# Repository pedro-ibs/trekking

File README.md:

# Trekking project
Desenvolvimento de um robô rádio-controlado/autônomo da moralidade “trekking”

Nos arquivos [anteriores-descontinuados](./anteriores-descontinuados/) e nos demais arquivos deste repositório podem conter os termos `rv1` e `rv2` eles estão referindo a versões anteriores do robô sendo `Robô versão 1` `Robô versão 2`.

<br>

Apresentações anteriores relaionadas:
 * [**#CPBR16** - Trabalhando com Unidades de medidas Inerciais (IMU) ](https://garoa.net.br/wiki/Dumont_Hackerspace_na_Campus_Party_2024)
 * [ **#CPBR15** - Construindo um Robô Trekking - versão 2.0](https://www.youtube.com/watch?v=lGhopql1V54)
 * [ **#CPBR14** - Construção de um robo rádio controlado](https://www.youtube.com/watch?v=8P9nPsCdVAc)

<br> <br> <br>

### **Robô versão 3**:

<br>

### **Robô versão 2**: 

<br>

### **Robô versão 1**:

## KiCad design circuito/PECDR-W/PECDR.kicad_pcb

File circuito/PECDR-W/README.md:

# **PECDR** - **P**lataforma **E**letrónica de **C**ontrole **D**istribuído em **R**ede 

A proposta deste circuito é distribuir o controle em subsistemas utilizando rede sem fio ou por meio da comunicação RS485. Conta com a `raspberry pi pico` modelo comum ou `W`. e diversos periféricos possibilitando atuar em trabalhos variados.

### **Elementos**:
 * O circuito embarca uma `raspberry pi pico` modelo comum ou `W`;
 * Uma fonte dc-dc buck step down 3V3 3A;
 * Driver de potência  L298N (com seleção de tensão de operação entre VCC e 3V3);
 * Interface de comunicação RS485;
 * Disponibiliza GPIOS para uso geral; 
 * Expansão para o MPU9250/6500;

<br>

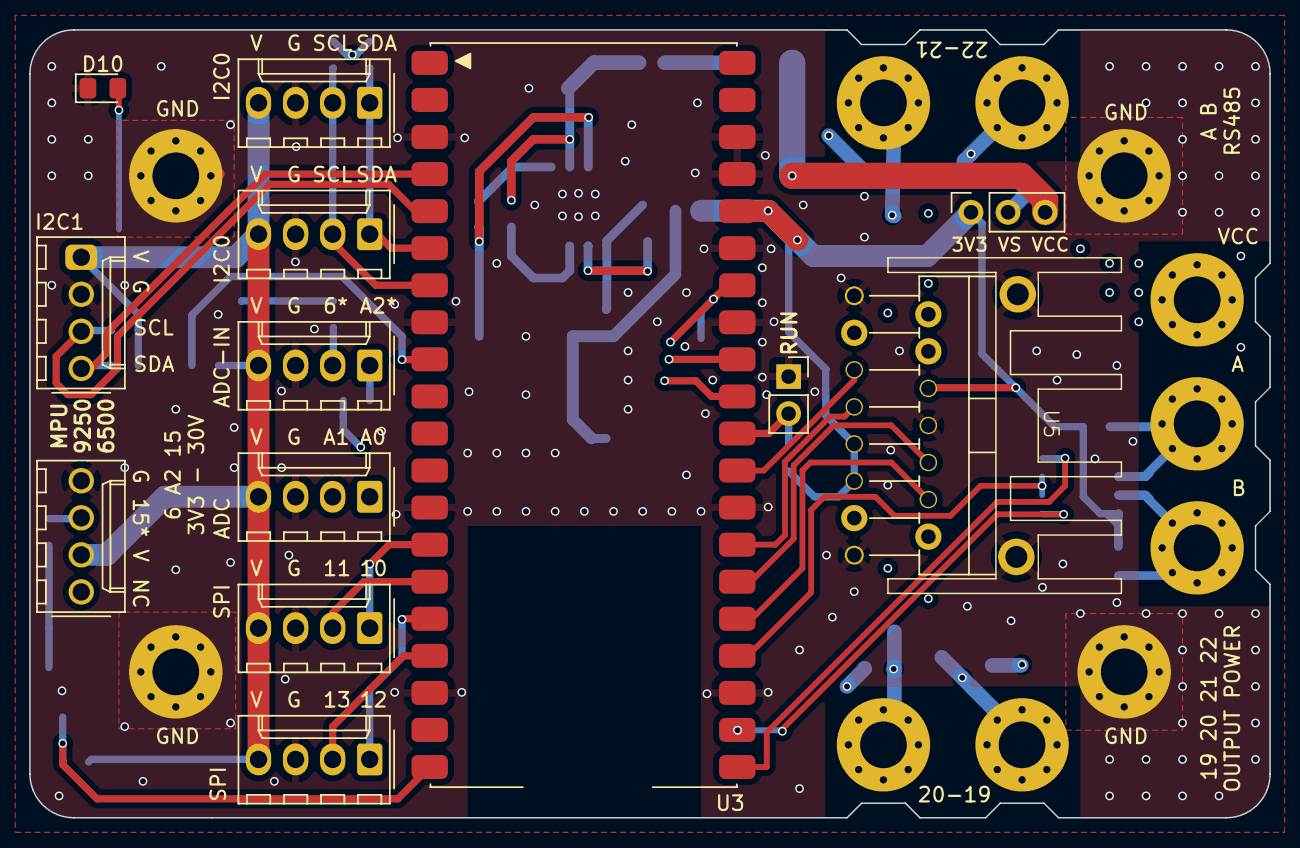
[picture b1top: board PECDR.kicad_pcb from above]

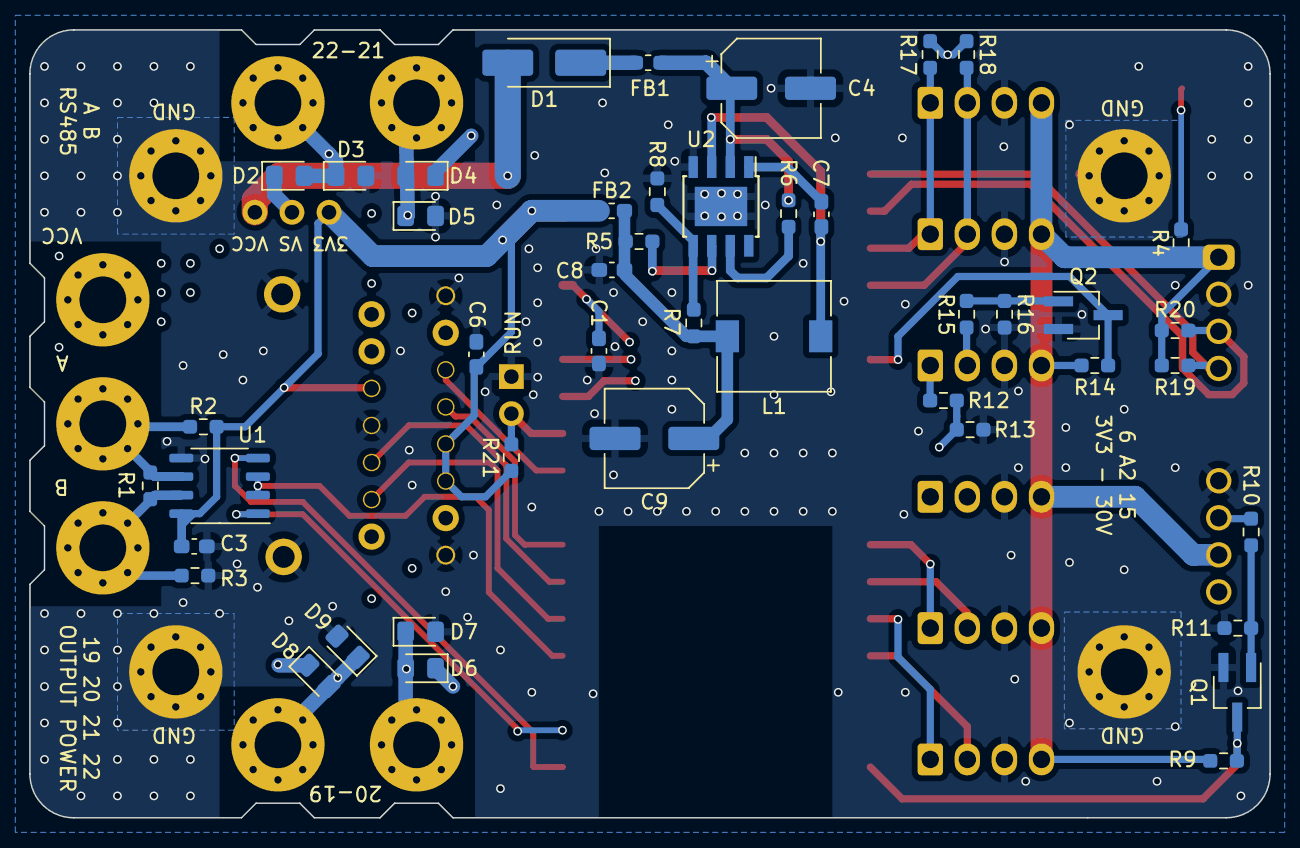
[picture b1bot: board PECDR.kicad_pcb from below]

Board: 4 copper layers, 85.0 x 54.0 mm, 68 parts (44 on the bottom side), 45 nets.

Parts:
C1: 10pF; C_0603_1608Metric_Pad1.08x0.95mm_HandSolder
C3, C6, C7, C8: 100nF; C_0603_1608Metric_Pad1.08x0.95mm_HandSolder
C4: 100uF 25V; CP_Elec_6.3x7.7
C9: 100uF 6V3; CP_Elec_6.3x7.7
D1: B340A; D_SMA_Handsoldering
D2, D3, D4, D5, D6, D7, D8, D9: B340A; D_0805_2012Metric_Pad1.15x1.40mm_HandSolder
D10: IHM; LED_0805_2012Metric_Pad1.15x1.40mm_HandSolder
FB1, FB2: Ferrite; L_0603_1608Metric_Pad1.05x0.95mm_HandSolder
J1: O2; MountingHole_3.2mm_M3_Pad_Via
J2: O4; MountingHole_3.2mm_M3_Pad_Via
J3: O1; MountingHole_3.2mm_M3_Pad_Via
J4: VCC; MountingHole_3.2mm_M3_Pad_Via
J5, J6: GP-I2C0; Molex_KK-254_AE-6410-04A_1x04_P2.54mm_Vertical
J7: GP-IN1; Molex_KK-254_AE-6410-04A_1x04_P2.54mm_Vertical
J8: GP/IN-ADC; Molex_KK-254_AE-6410-04A_1x04_P2.54mm_Vertical
J9: GP-ADC; Molex_KK-254_AE-6410-04A_1x04_P2.54mm_Vertical
J10, J11: GP-SPI; Molex_KK-254_AE-6410-04A_1x04_P2.54mm_Vertical
J12: O3; MountingHole_3.2mm_M3_Pad_Via
J13, J13#2, J13#3, J13#4: GND; MountingHole_3.2mm_M3_Pad_Via
J14: A; MountingHole_3.2mm_M3_Pad_Via
J15: B; MountingHole_3.2mm_M3_Pad_Via
J16: VS-SELECT; PinSocket_1x03_P2.54mm_Vertical
J17: GP-I2C1; Molex_KK-254_AE-6410-04A_1x04_P2.54mm_Vertical
JP1: RUM; PinSocket_1x02_P2.54mm_Vertical
L1: 10uH; L_Wuerth_WE-PD-Typ-M-Typ-S
Q1, Q2: BC848ALT1; SOT-23W_Handsoldering
R1: 4k7; R_0603_1608Metric_Pad0.98x0.95mm_HandSolder
R2, R3: 4K7; R_0603_1608Metric_Pad0.98x0.95mm_HandSolder
R4: 1K; R_0603_1608Metric_Pad0.98x0.95mm_HandSolder
R5, R17, R18, R19, R20, R21: 10k; R_0603_1608Metric_Pad0.98x0.95mm_HandSolder
R6: 100k; R_0603_1608Metric_Pad0.98x0.95mm_HandSolder
R7: 26k1 1%; R_0603_1608Metric_Pad0.98x0.95mm_HandSolder
R8: 10k 1%; R_0603_1608Metric_Pad0.98x0.95mm_HandSolder
R9, R10, R11, R12, R13, R14, R15, R16: 10K; R_0603_1608Metric_Pad0.98x0.95mm_HandSolder
U1: MAX485CSA+; SOP-8_3.9x4.9mm_P1.27mm
U2: FR9889; Diodes_PSOP-8
U3: RPI-PICO; RPI-PICO-SMD
U5: L298N; SINK-L298N

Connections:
+3V3: C3.1, C6.1, FB2.2, J5.4, J6.4, J7.2, J8.4, J9.4, J10.4, J11.4, J16.1, J17.4, R2.1, R4.1, R9.1, R14.1, R17.1, R18.1, R19.1, R20.1, R21.1, U1.8 (VCC), U3.36 (3V3), U5.6 (EnA), U5.9 (Vss), U5.11 (EnB)
/A: J14.1, R1.1, R2.2, U1.6 (A)
/ADC2: J8.1, R12.1
/B: J15.1, R1.2, R3.1, U1.7 (B)
/DriverInput: U1.4 (DI), U3.21 (GP16)
/G15: Q1.3 (C), R9.2, U3.20 (GP15)
/GP6: Q2.3 (C), R14.2, U3.9 (GP6)
/GP19: U3.25 (GP19), U5.12 (IN4)
/GP20: U3.26 (GP20), U5.10 (IN3)
/GP21: U3.27 (GP21), U5.7 (IN2)
/GP22: U3.29 (GP22), U5.5 (IN1)
/GP26-ADC0-SDA1: J9.1, U3.31 (GP26)
/GP27-ADC1-SCL1: J9.2, U3.32 (GP27)
/GP28-ADC2: C1.1, R12.2, R13.1, U3.34 (GP28)
/IN1: J7.3, R10.1
/IN2: J8.2, R15.1
/InputOutputEnable: U1.2 (~RE), U1.3 (DE), U3.24 (GP18)
/OUT1: D2.2 (A), D3.1 (K), J3.1, U5.2 (OUT1)
/OUT2: D4.2 (A), D5.1 (K), J1.1, U5.3 (OUT2)
/OUT3: D6.2 (A), D7.1 (K), J12.1, U5.13 (OUT3)
/OUT4: D8.2 (A), D9.1 (K), J2.1, U5.14 (OUT4)
/RUN: JP1.2 (B), R21.2, U3.30 (RUN)
/RXD0-SCL0-CS1-GP13: J11.2, U3.17 (GP13)
/RXD1-SCL0-CS0-GP5: J5.2, J6.2, R18.2, U3.7 (GP5_SCL0)
/ReceiverOutput: U1.1 (RO), U3.22 (GP17)
/SCL1-TX0-GP3: J17.2, R20.2, U3.5 (GP3)
/SCL1-TX1-GP11: J10.2, U3.15 (GP11)
/SDA1-SCK0-GP2: J17.1, R19.2, U3.4 (GP2)
/SDA1-SCK1-GP10: J10.1, U3.14 (GP10)
/TXD0-SDA0-RX1-GP12: J11.1, U3.16 (GP12)
/TXD1-SDA0-RX0-GP4: J5.1, J6.1, R17.2, U3.6 (GP4_SDA0)
GND: C1.2, C3.2, C4.2, C6.2, C8.2, C9.2, D3.2 (A), D5.2 (A), D7.2 (A), D9.2 (A), D10.1 (K), J5.3, J6.3, J7.4, J8.3, J9.3, J10.3, J11.3, J13.1, J13#2.1, J13#3.1, J13#4.1, J17.3, JP1.1 (A), Q1.2 (E), Q2.2 (E), R3.2, R8.1, R11.2, R13.2, R16.2, U1.5 (GND), U2.4 (GND), U2.9 (GND_TAP), U3.3 (GND), U3.8 (GND), U3.13 (GND), U3.18 (GND), U3.23 (GND), U3.28 (GND), U3.33 (GND), U3.35 (ADC_VREF), U3.37 (3V3_EN), U3.38 (GND), U5.1 (SENSE_A), U5.8 (GND), U5.15 (SENSE_B)
unnamed: C8.1, C9.1, FB2.1, L1.2, R5.2, R7.2
unnamed: D1.1 (K), FB1.2
unnamed: D10.2 (A), R4.2
unnamed: Q1.1 (B), R10.2, R11.1
unnamed: Q2.1 (B), R15.2, R16.1
unnamed: C7.2, U2.1 (BST)
unnamed: R7.1, R8.2, U2.5 (FB)
unnamed: C7.1, L1.1, U2.3 (LX)
unnamed: R5.1, U2.6 (PG)
unnamed: C4.1, FB1.1, R6.1, U2.2 (VIN)
unnamed: R6.2, U2.7 (~SHDN)
VCC: D1.2 (A), J4.1, J16.3
VS: D2.1 (K), D4.1 (K), D6.1 (K), D8.1 (K), J16.2, U5.4 (Vs)

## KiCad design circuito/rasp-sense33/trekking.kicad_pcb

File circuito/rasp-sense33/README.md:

# Trekking project

<hr>

## *Descrição*

Com a demanda de otimizar espaço, fontes mais potentes e flexibilizar o dispositivo de controle **main** como da *raspberry pi* para *jetson nano* por exemplo, optei em projetar outro circuito,  com os seguintes aspectos e alterações:
 
 * As fontes são quase que totalmente removidas para se adaptar de forma mais útil a um dispositivo de controle main  que demande mais potência,
 
 * Adição do *Arduino ble 33 sense* integrando o sistema de aquisição controle em um único local.

 * Adição de saídas de potências para manipular atuadores genéricos, como o motor do lidar.
 
 * Conectores específicos para trabalhar com os encoders.

<br>
<hr>

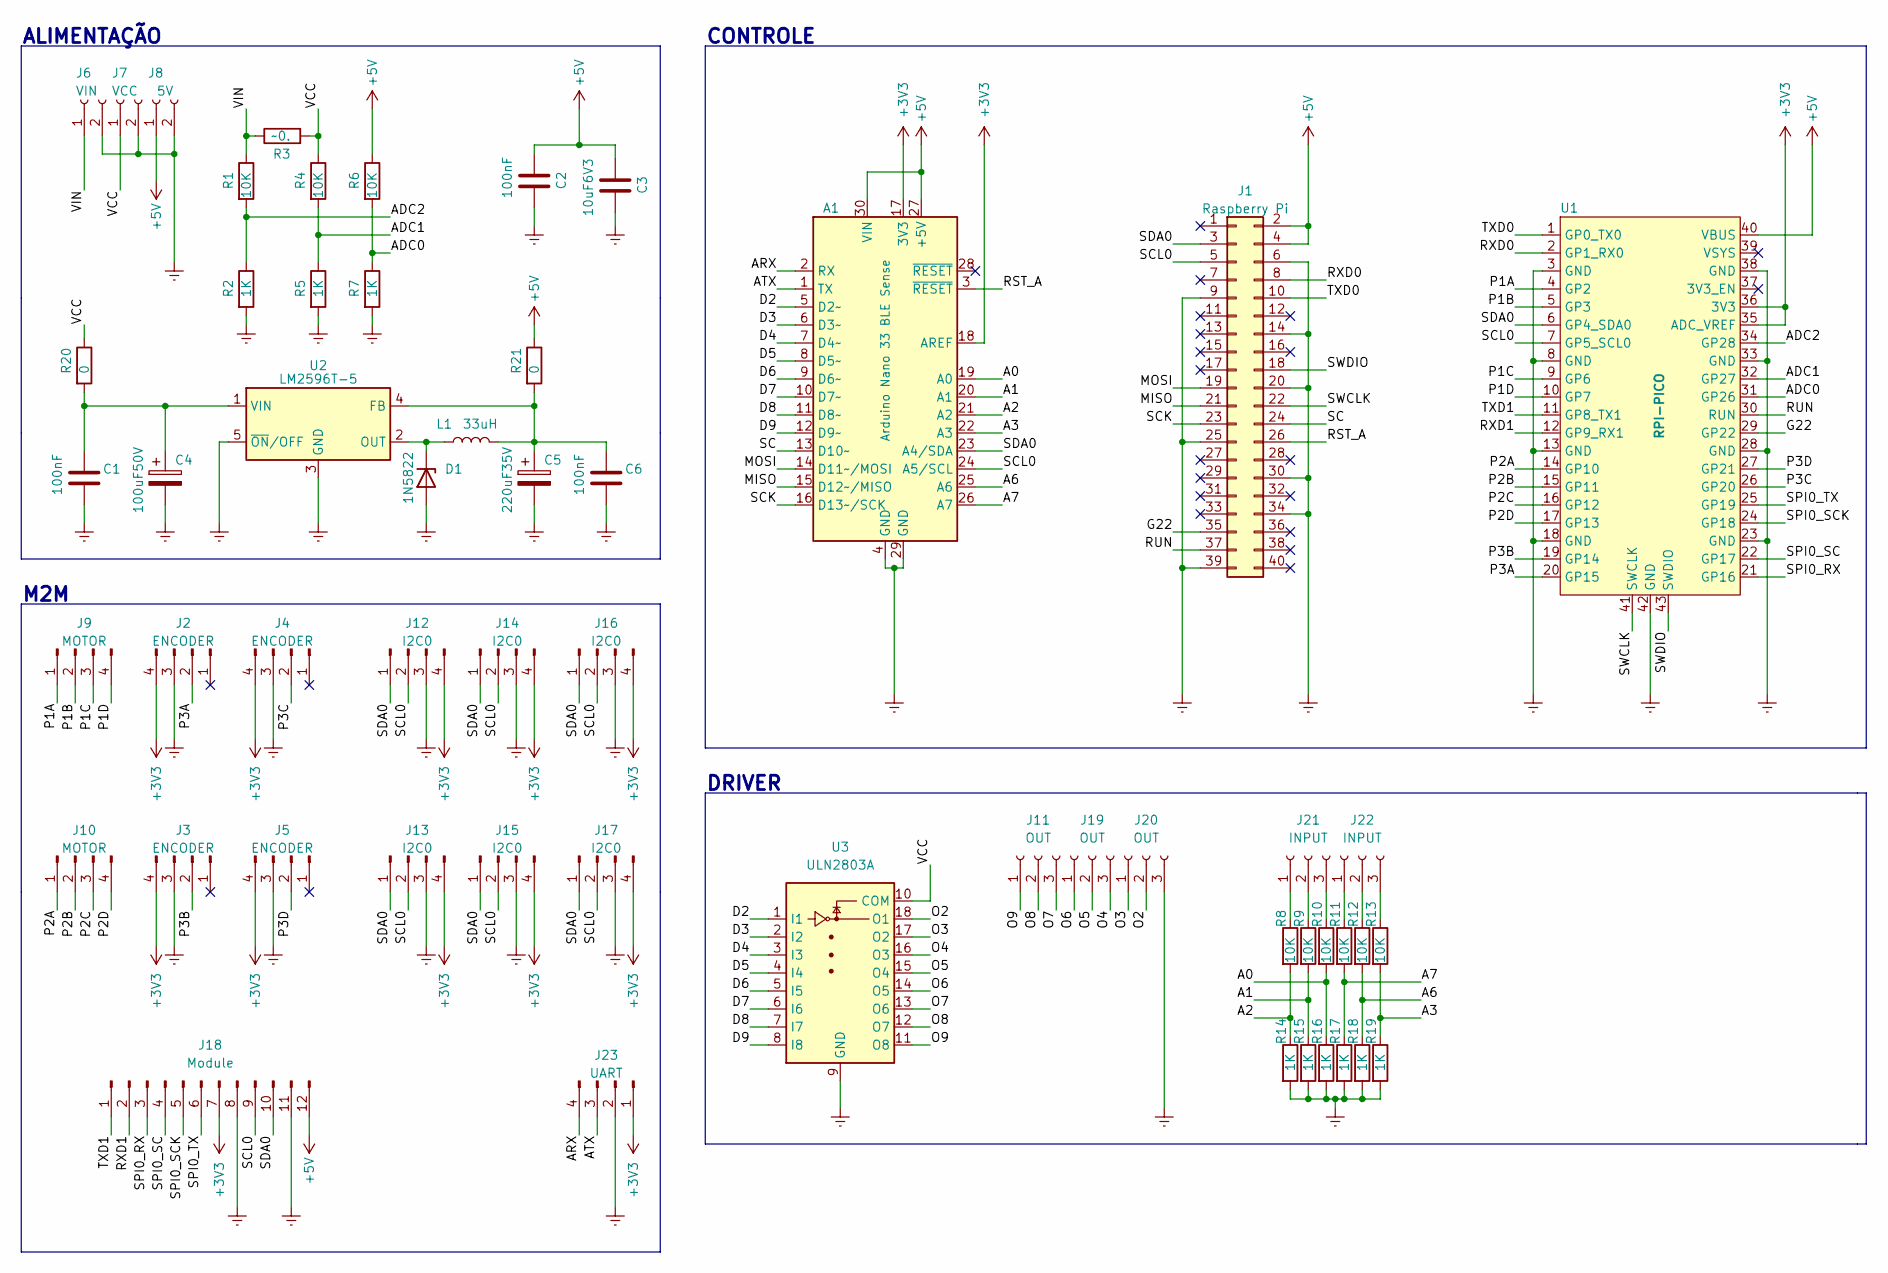
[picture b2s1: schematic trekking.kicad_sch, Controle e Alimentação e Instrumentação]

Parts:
A1: Arduino Nano 33 BLE Sense; Arduino_Nano
C1, C2, C6: 100nF; C_0805_2012Metric_Pad1.18x1.45mm_HandSolder
C3: 10uF6V3; C_0805_2012Metric_Pad1.18x1.45mm_HandSolder
C4: 100uF50V; CP_Elec_8x10
C5: 220uF35V; CP_Elec_8x10
D1: 1N5822; My_D_MELF-RM10_Universal_Handsoldering_2
J1: Raspberry Pi; PinHeader_2x20_P2.54mm_Vertical
J2, J3, J4, J5: ENCODER; Molex_KK-254_AE-6410-04A_1x04_P2.54mm_Vertical
J6: VIN; AK300-2
J7: VCC; AK300-2
J8: 5V; AK300-2
J9, J10: MOTOR; Molex_KK-254_AE-6410-04A_1x04_P2.54mm_Vertical
J11, J19, J20: OUT; CONN5mm-3
J12, J13, J14, J15, J16, J17: I2C0; Molex_KK-254_AE-6410-04A_1x04_P2.54mm_Vertical
J18: Module; PinHeader_1x12_P2.54mm_Vertical
J21, J22: INPUT; CONN5mm-3
J23: UART; Molex_KK-254_AE-6410-04A_1x04_P2.54mm_Vertical
L1: 33uH; L_12x12mm_H8mm
R1, R4, R6, R8, R9, R10, R11, R12, R13: 10K; R_0805_2012Metric_Pad1.20x1.40mm_HandSolder
R2, R5, R7, R14, R15, R16, R17, R18, R19: 1K; R_0805_2012Metric_Pad1.20x1.40mm_HandSolder
R3: ~0.; R_1206_3216Metric_Pad1.30x1.75mm_HandSolder
R20, R21: 0; R_0805_2012Metric_Pad1.20x1.40mm_HandSolder
U1: RPI-PICO; RPI-PICO-SMD
U2: LM2596T-5; TO-263-5_TabPin3
U3: ULN2803A; SOIC-18W_7.5x11.6mm_P1.27mm

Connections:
+3V3: A1.17 (3V3), A1.18 (AREF), J2.4, J3.4, J4.4, J5.4, J12.4, J13.4, J14.4, J15.4, J16.4, J17.4, J18.7, J23.1, U1.35 (ADC_VREF), U1.36 (3V3)
+5V: A1.27 (+5V), A1.30 (VIN), C2.1, C3.1, J1.2, J1.4, J8.1, J18.12, R6.1, R21.1, U1.40 (VBUS)
/A0: A1.19 (A0), R10.2, R16.1
/A1: A1.20 (A1), R9.2, R15.1
/A2: A1.21 (A2), R8.2, R14.1
/A3: A1.22 (A3), R13.2, R19.1
/A6: A1.25 (A6), R12.2, R18.1
/A7: A1.26 (A7), R11.2, R17.1
/ADC0: R6.2, R7.1, U1.31 (GP26)
/ADC1: R4.2, R5.1, U1.32 (GP27)
/ADC2: R1.2, R2.1, U1.34 (GP28)
/ARX: A1.2 (RX), J23.4
/ATX: A1.1 (TX), J23.3
/D2: A1.5 (D2~), U3.1 (I1)
/D3: A1.6 (D3~), U3.2 (I2)
/D4: A1.7 (D4~), U3.3 (I3)
/D5: A1.8 (D5~), U3.4 (I4)
/D6: A1.9 (D6~), U3.5 (I5)
/D7: A1.10 (D7~), U3.6 (I6)
/D8: A1.11 (D8~), U3.7 (I7)
/D9: A1.12 (D9~), U3.8 (I8)
/G22: J1.35, U1.29 (GP22)
/MISO: A1.15 (D12~/MISO), J1.21
/MOSI: A1.14 (D11~/MOSI), J1.19
/O2: J20.2, U3.18 (O1)
/O3: J20.1, U3.17 (O2)
/O4: J19.3, U3.16 (O3)
/O5: J19.2, U3.15 (O4)
/O6: J19.1, U3.14 (O5)
/O7: J11.3, U3.13 (O6)
/O8: J11.2, U3.12 (O7)
/O9: J11.1, U3.11 (O8)
/P1A: J9.1, U1.4 (GP2)
/P1B: J9.2, U1.5 (GP3)
/P1C: J9.3, U1.9 (GP6)
/P1D: J9.4, U1.10 (GP7)
/P2A: J10.1, U1.14 (GP10)
/P2B: J10.2, U1.15 (GP11)
/P2C: J10.3, U1.16 (GP12)
/P2D: J10.4, U1.17 (GP13)
/P3A: J2.2, U1.20 (GP15)
/P3B: J3.2, U1.19 (GP14)
/P3C: J4.2, U1.26 (GP20)
/P3D: J5.2, U1.27 (GP21)
/RST_A: A1.3 (~RESET), J1.26
/RUN: J1.37, U1.30 (RUN)
/RXD0: J1.8, U1.2 (GP1_RX0)
/RXD1: J18.2, U1.12 (GP9_RX1)
/SC: A1.13 (D10~), J1.24
/SCK: A1.16 (D13~/SCK), J1.23
/SCL0: A1.24 (A5/SCL), J1.5, J12.2, J13.2, J14.2, J15.2, J16.2, J17.2, J18.9, U1.7 (GP5_SCL0)
/SDA0: A1.23 (A4/SDA), J1.3, J12.1, J13.1, J14.1, J15.1, J16.1, J17.1, J18.10, U1.6 (GP4_SDA0)
/SPI0_RX: J18.3, U1.21 (GP16)
/SPI0_SC: J18.4, U1.22 (GP17)
/SPI0_SCK: J18.5, U1.24 (GP18)
/SPI0_TX: J18.6, U1.25 (GP19)
/SWCLK: J1.22, U1.41 (SWCLK)
/SWDIO: J1.18, U1.43 (SWDIO)
/TXD0: J1.10, U1.1 (GP0_TX0)
/TXD1: J18.1, U1.11 (GP8_TX1)
/VCC: J7.1, R3.2, R4.1, R20.1, U3.10 (COM); also elsewhere on the board
/VIN: J6.1, R1.1, R3.1; also elsewhere on the board
Earth: A1.4 (GND), A1.29 (GND), C1.2, C2.2, C3.2, C4.2, C5.2, C6.2, D1.2 (A), J1.6, J1.9, J1.14, J1.20, J1.25, J1.30, J1.34, J1.39, J2.3, J3.3, J4.3, J5.3, J6.2, J7.2, J8.2, J12.3, J13.3, J14.3, J15.3, J16.3, J17.3, J18.8, J18.11, J20.3, J23.2, R2.2, R5.2, R7.2, R14.2, R15.2, R16.2, R17.2, R18.2, R19.2, U1.3 (GND), U1.8 (GND), U1.13 (GND), U1.18 (GND), U1.23 (GND), U1.28 (GND), U1.33 (GND), U1.38 (GND), U1.42 (GND), U2.3 (GND), U2.5 (~ON/OFF), U3.9 (GND)
unnamed: C1.1, C4.1, R20.2, U2.1 (VIN)
unnamed: C5.1, C6.1, L1.2, R21.2, U2.4 (FB)
unnamed: D1.1 (K), L1.1, U2.2 (OUT)
unnamed: J21.1, R8.1
unnamed: J21.2, R9.1
unnamed: J21.3, R10.1
unnamed: J22.1, R11.1
unnamed: J22.2, R12.1
unnamed: J22.3, R13.1

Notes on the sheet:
ALIMENTAÇÃO
CONTROLE
M2M
DRIVER

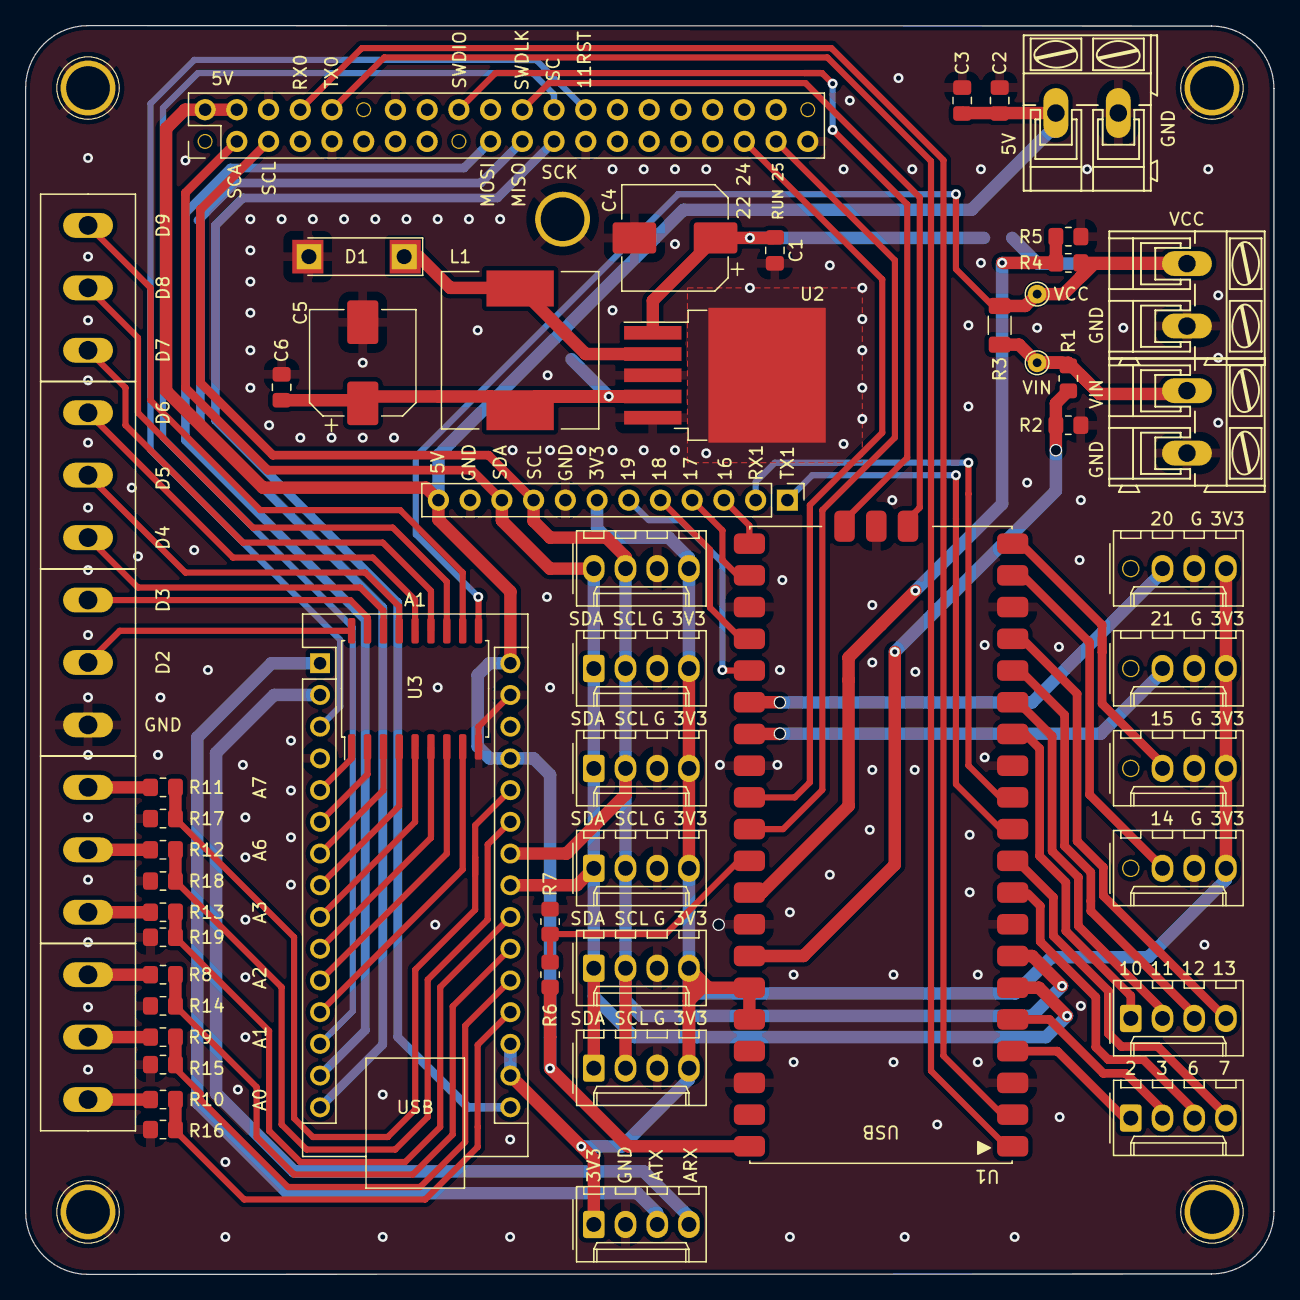
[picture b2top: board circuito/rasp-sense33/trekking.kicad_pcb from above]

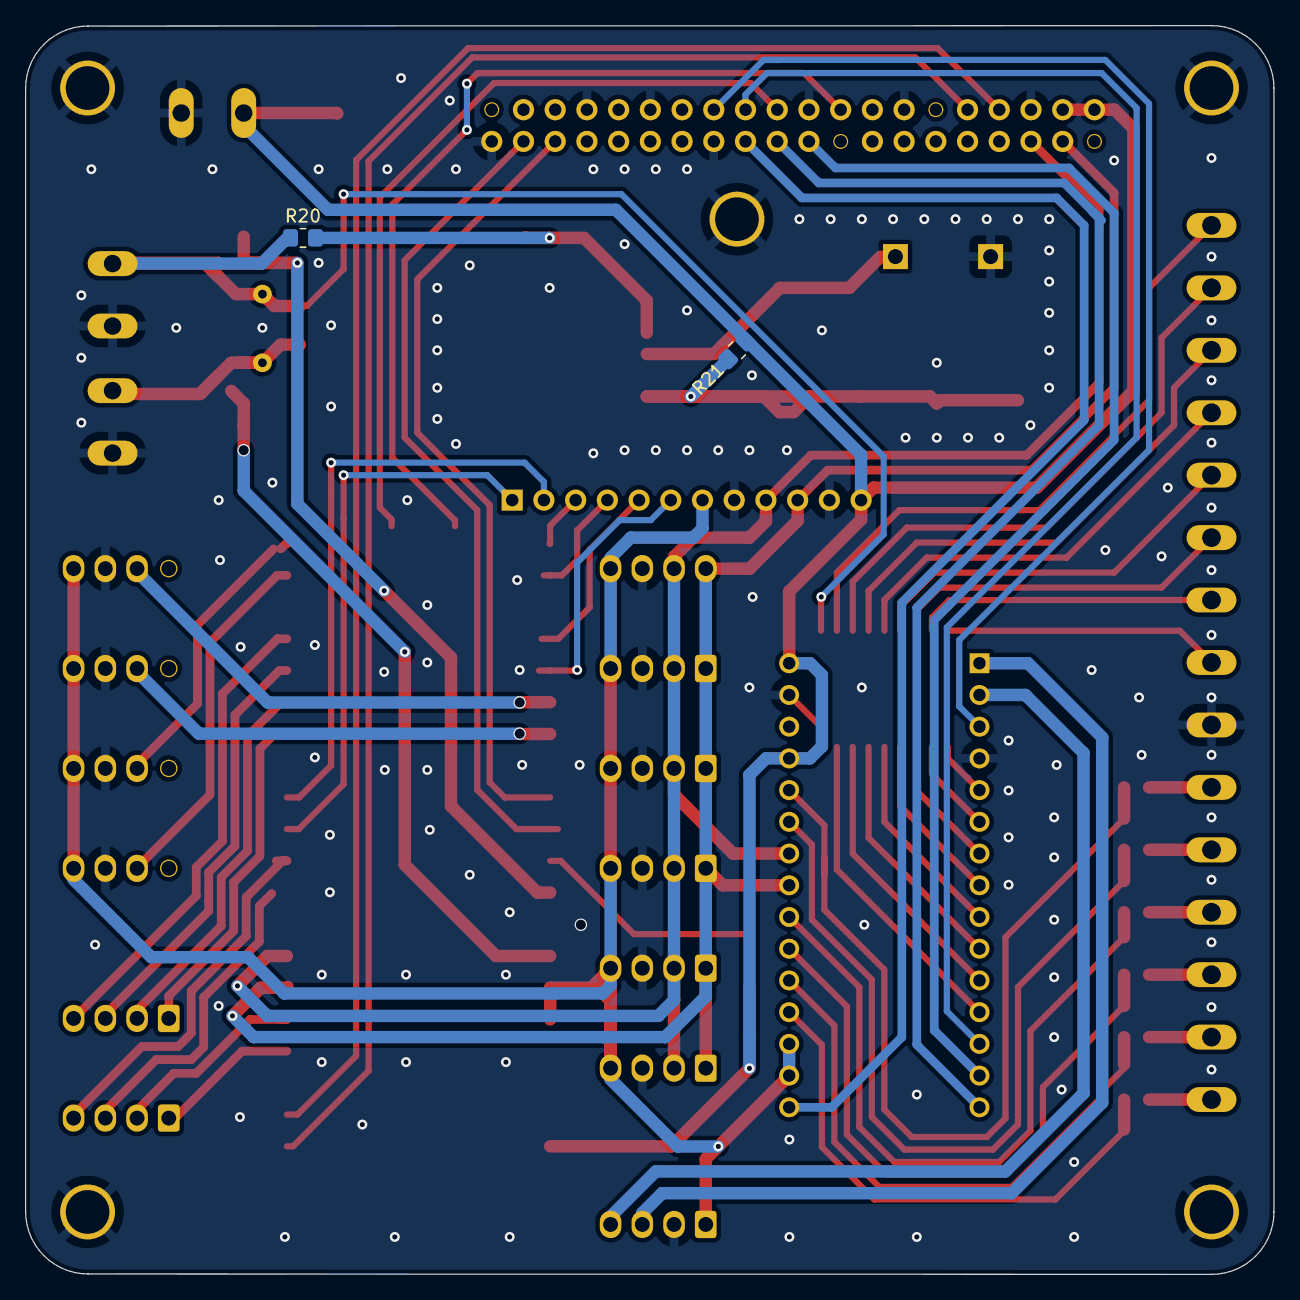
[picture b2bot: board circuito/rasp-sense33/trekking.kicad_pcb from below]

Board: 2 copper layers, 100.0 x 100.0 mm, 58 parts (2 on the bottom side), 72 nets.

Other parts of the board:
VCC: TestPoint_THTPad_D1.5mm_Drill0.7mm
VIN: TestPoint_THTPad_D1.5mm_Drill0.7mm

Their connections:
/VCC: VCC.1; also elsewhere on the board
/VIN: VIN.1; also elsewhere on the board

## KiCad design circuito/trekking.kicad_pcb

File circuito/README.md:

# **ESQUEMA GERAL DA ALIMENTAÇÃO E CONEXÇÕES DO ROBÔ**

<br>

### **ALIMENTAÇÃO GERAL**
A chave `SELETOR` muda se a bateria passrá pelo voltimetro-amperimetro, ou se firará em paralelo com a carga, permitindo assim monitorar o carregamento da bateria. Também com as chaves `CIRCUITO COMUTADOR` e `CIRCUITO POTÊNCIA` permite ligar ou desligar um sistema independentemente do outro. Essas opções existem para facilitar o desenvolvimento e manutenção do robô

<br>

<br> <br>

### **ALIMENTAÇÃO DOS SUBSISTEMAS**
Para o Robô a linha de `POTÊNCIA` é considerada a de 12V, que irá alimentar os motores e atuadores que demandam uma corrente elevada. Já a linha `COMPUTADOR` é responsável por alimentar o sistema de controle principal e alguns subsistemas.

<br>

<br> <br>

### **ALIMENTAÇÃO DOS SUBSISTEMAS**
O robô contém alguns subsistemas, dois reservados para controlar os conjuntos de motores esquerdos e direitos, e um responsável pelo controle de ativação e controle ativo sensores e atuadores, também faz a aquisição de alguns sensores.

<br>

<br>

### **Topologia das conexõesdo dos motores**

<br> <br>

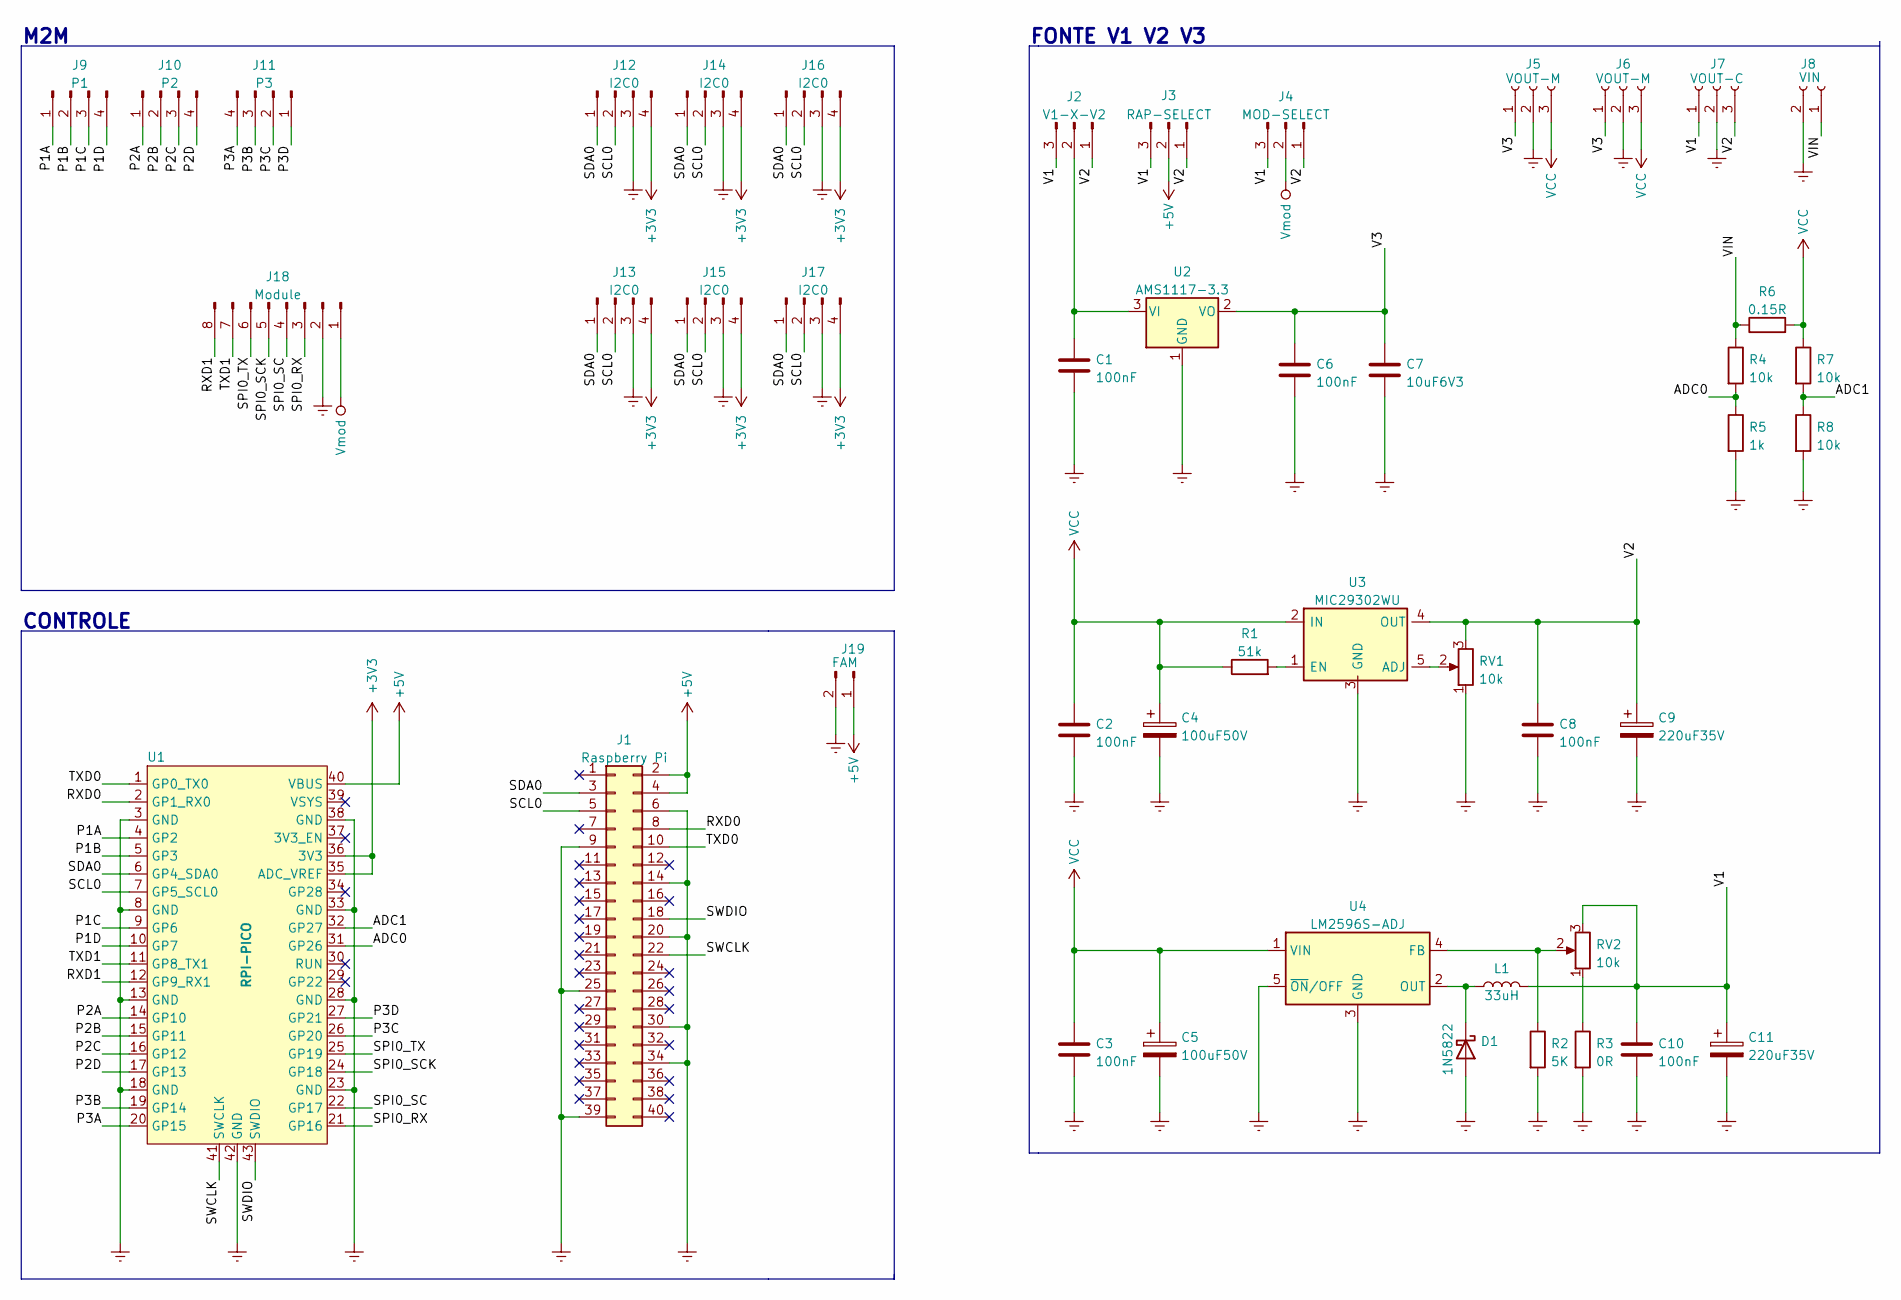
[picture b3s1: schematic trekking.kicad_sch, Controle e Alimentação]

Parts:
C1: 100nF
C2, C3, C6, C8, C10: 100nF; C_0805_2012Metric_Pad1.18x1.45mm_HandSolder
C4, C5: 100uF50V; CP_Elec_8x10
C7: 10uF6V3; C_0805_2012Metric_Pad1.18x1.45mm_HandSolder
C9, C11: 220uF35V; CP_Elec_8x10
D1: 1N5822; D_3220_8050Metric_Pad2.65x5.15mm_HandSolder
J1: Raspberry Pi; PinHeader_2x20_P2.54mm_Vertical
J2: V1-X-V2; PinHeader_1x03_P2.54mm_Vertical
J3: RAP-SELECT; PinHeader_1x03_P2.54mm_Vertical
J4: MOD-SELECT; PinHeader_1x03_P2.54mm_Vertical
J5, J6: VOUT-M; CONN5mm-3
J7: VOUT-C; CONN5mm-3
J8: VIN; AK300-2
J9: P1; Molex_KK-254_AE-6410-04A_1x04_P2.54mm_Vertical
J10: P2; Molex_KK-254_AE-6410-04A_1x04_P2.54mm_Vertical
J11: P3; Molex_KK-254_AE-6410-04A_1x04_P2.54mm_Vertical
J12, J13, J14, J15, J16, J17: I2C0; Molex_KK-254_AE-6410-04A_1x04_P2.54mm_Vertical
J18: Module; PinHeader_1x08_P2.54mm_Vertical
J19: FAM; PinHeader_1x02_P2.54mm_Vertical
L1: 33uH; L_12x12mm_H8mm
R1: 51k; R_0805_2012Metric_Pad1.20x1.40mm_HandSolder
R2: 5K; R_0805_2012Metric_Pad1.20x1.40mm_HandSolder
R3: 0R; R_0805_2012Metric_Pad1.20x1.40mm_HandSolder
R4, R7, R8: 10k; R_0805_2012Metric_Pad1.20x1.40mm_HandSolder
R5: 1k; R_0805_2012Metric_Pad1.20x1.40mm_HandSolder
R6: 0.15R; R_2512_6332Metric_Pad1.40x3.35mm_HandSolder
RV1, RV2: 10k; Potentiometer_Bourns_3266Y_Vertical
U1: RPI-PICO; RPI-PICO-SMD
U2: AMS1117-3.3; SOT-223-3_TabPin2
U3: MIC29302WU; TO-263-5_TabPin3
U4: LM2596S-ADJ; TO-263-5_TabPin3

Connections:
+3V3: J12.4, J13.4, J14.4, J15.4, J16.4, J17.4, U1.35 (ADC_VREF), U1.36 (3V3)
+5V: J1.2, J1.4, J3.2, J19.1, U1.40 (VBUS)
/ADC0: R4.2, R5.1, U1.31 (GP26)
/ADC1: R7.2, R8.1, U1.32 (GP27)
/P1A: J9.1, U1.4 (GP2)
/P1B: J9.2, U1.5 (GP3)
/P1C: J9.3, U1.9 (GP6)
/P1D: J9.4, U1.10 (GP7)
/P2A: J10.1, U1.14 (GP10)
/P2B: J10.2, U1.15 (GP11)
/P2C: J10.3, U1.16 (GP12)
/P2D: J10.4, U1.17 (GP13)
/P3A: J11.4, U1.20 (GP15)
/P3B: J11.3, U1.19 (GP14)
/P3C: J11.2, U1.26 (GP20)
/P3D: J11.1, U1.27 (GP21)
/RXD0: J1.8, U1.2 (GP1_RX0)
/RXD1: J18.8, U1.12 (GP9_RX1)
/SCL0: J1.5, J12.2, J13.2, J14.2, J15.2, J16.2, J17.2, U1.7 (GP5_SCL0)
/SDA0: J1.3, J12.1, J13.1, J14.1, J15.1, J16.1, J17.1, U1.6 (GP4_SDA0)
/SPI0_RX: J18.3, U1.21 (GP16)
/SPI0_SC: J18.4, U1.22 (GP17)
/SPI0_SCK: J18.5, U1.24 (GP18)
/SPI0_TX: J18.6, U1.25 (GP19)
/SWCLK: J1.22, U1.41 (SWCLK)
/SWDIO: J1.18, U1.43 (SWDIO)
/TXD0: J1.10, U1.1 (GP0_TX0)
/TXD1: J18.7, U1.11 (GP8_TX1)
/V1: C10.1, C11.1, J2.3, J3.3, J4.3, J7.1, L1.2, RV2.3
/V2: C8.1, C9.1, J2.1, J3.1, J4.1, J7.3, RV1.3, U3.4 (OUT)
/V3: C6.1, C7.1, J5.1, J6.1, U2.2 (VO)
/VIN: J8.1, R4.1, R6.1
Earth: C1.2, C2.2, C3.2, C4.2, C5.2, C6.2, C7.2, C8.2, C9.2, C10.2, C11.2, D1.2 (A), J1.6, J1.9, J1.14, J1.20, J1.25, J1.30, J1.34, J1.39, J5.2, J6.2, J7.2, J8.2, J12.3, J13.3, J14.3, J15.3, J16.3, J17.3, J18.2, J19.2, R2.2, R3.2, R5.2, R8.2, RV1.1, U1.3 (GND), U1.8 (GND), U1.13 (GND), U1.18 (GND), U1.23 (GND), U1.28 (GND), U1.33 (GND), U1.38 (GND), U1.42 (GND), U2.1 (GND), U3.3 (GND), U4.3 (GND), U4.5 (~ON/OFF)
unnamed: C1.1, J2.2, U2.3 (VI)
unnamed: D1.1 (K), L1.1, U4.2 (OUT)
unnamed: R1.2, U3.1 (EN)
unnamed: R2.1, RV2.2, U4.4 (FB)
unnamed: R3.1, RV2.1
unnamed: RV1.2, U3.5 (ADJ)
VCC: C2.1, C3.1, C4.1, C5.1, J5.3, J6.3, R1.1, R6.2, R7.1, U3.2 (IN), U4.1 (VIN)
Vmod: J4.2, J18.1

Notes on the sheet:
CONTROLE
M2M
FONTE V1 V2 V3

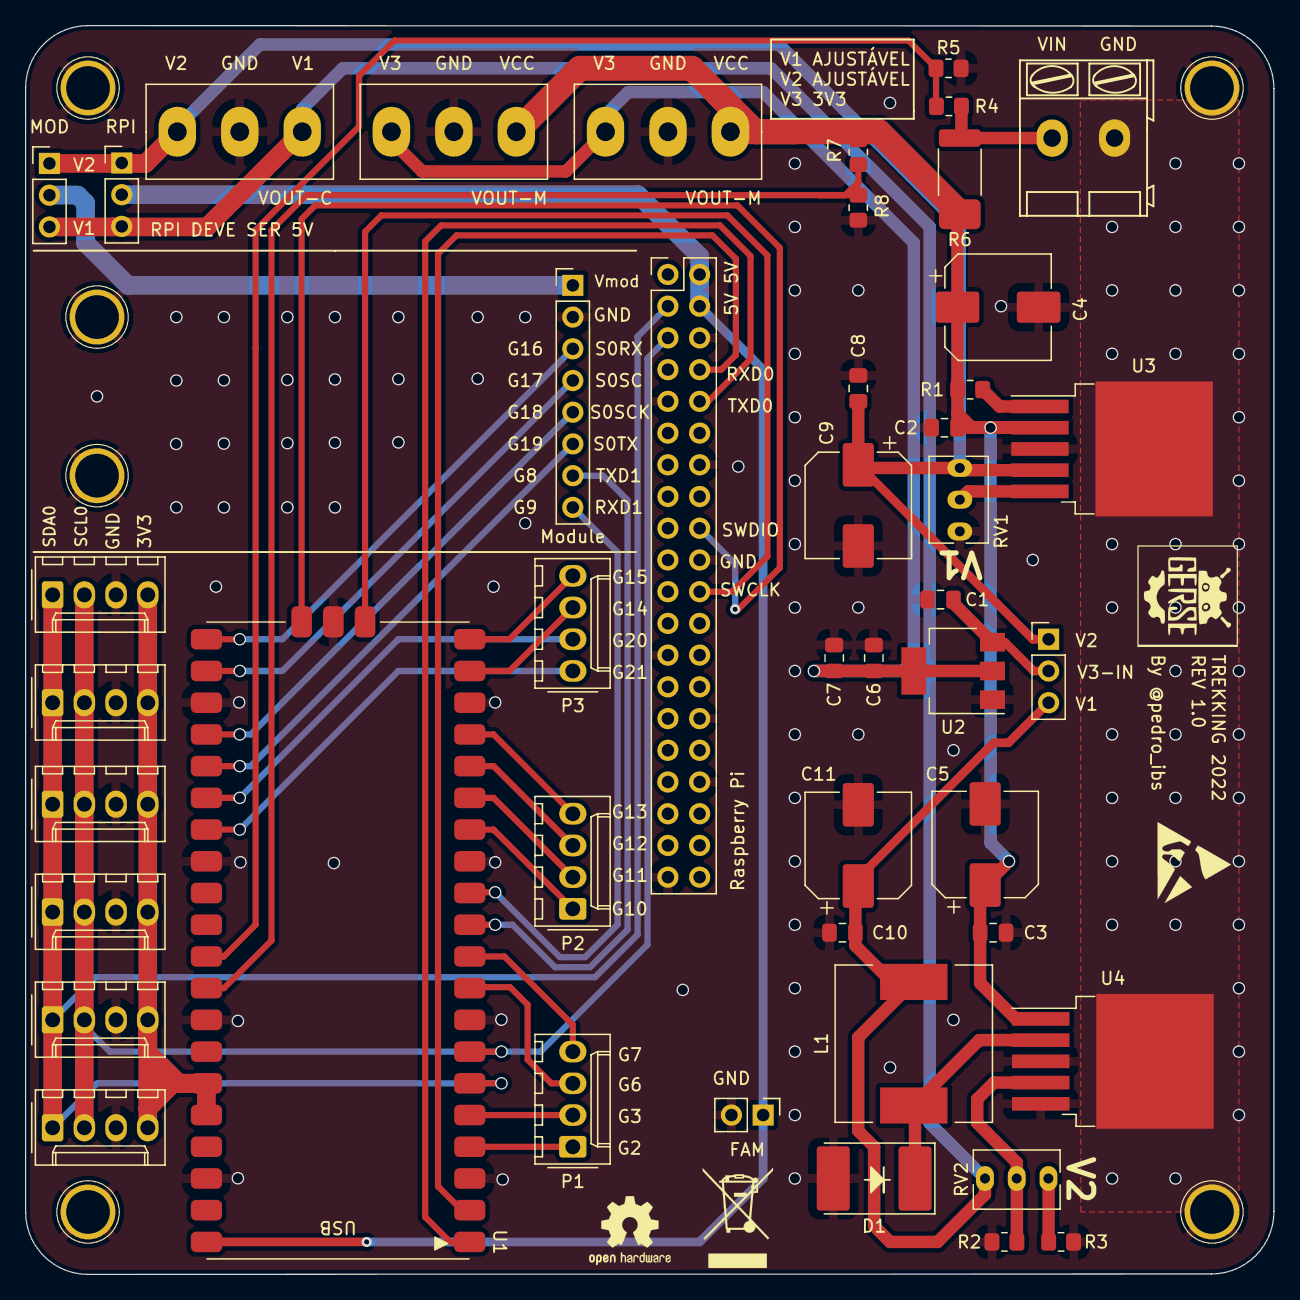
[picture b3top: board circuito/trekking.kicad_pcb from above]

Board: 2 copper layers, 100.0 x 100.0 mm, 46 parts (0 on the bottom side), 41 nets.

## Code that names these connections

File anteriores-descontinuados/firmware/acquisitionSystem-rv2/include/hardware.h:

/**
 * hardware.h
 *
 *  @date Created at:	26/03/2023 17:39:32
 *	@author:	Pedro Igor B. S.
 *	@email:		pibscontato@gmail.com
 * 	GitHub:		https://github.com/pedro-ibs
 * 	tabSize:	8
 *
 * #######################################################################
 *
 *   Copyright (C) Pedro Igor B. S 2021
 * -------------------------------------------------------------------
 *
 *   Licença: GNU GPL 2
 * -------------------------------------------------------------------
 *   This program is free software; you can redistribute it and/or
 *   modify it under the terms of the GNU General Public License as
 *   published by the Free Software Foundation; version 2 of the
 *   License.
 *
 *   This program is distributed in the hope that it will be useful,
 *   but WITHOUT ANY WARRANTY; without even the implied warranty of
 *   MERCHANTABILITY or FITNESS FOR A PARTICULAR PURPOSE.  See the
 *   GNU General Public License for more details.
 * -------------------------------------------------------------------
 * #######################################################################
 *
 * Definições dos pinos utilizados 
 *
 */

/* Includes ---------------------------------------------------------------------------------------------------------------------------------------------*/
#include <Arduino.h>


#ifndef hardware_H_
#define hardware_H_

/* settings ----------------------------------------------------------------------------------------------------------------------------------------------*/
/* Definition --------------------------------------------------------------------------------------------------------------------------------------------*/

#define PIN_OUT1	D2
#define PIN_OUT2	D3
#define PIN_OUT3	D4
#define PIN_OUT4	D5
#define PIN_OUT5	D6
#define PIN_OUT6	D7
#define PIN_OUT7	D8
#define PIN_OUT8	D9


			

#endif /* hardware_H_ */

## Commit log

2022-05-27 projeto mecânico inicial
2022-05-27 listas de materias no README
2022-05-27 att lista de materias
2022-05-27 att README
2022-05-27 correção do encaixa para do motor 'v-slot-2020-mancal-motor' rebaixo de .12mm ( resolução da Ender 3 )
2022-05-28 coleta de medidas
2022-05-29 nomas medicasa e novos v-slot-2020-trem
2022-05-29 correção v-slot-2020-trem-6mm
2022-05-29 correção medidas ponte-h
2022-05-29 criado v-slot-2020-suporte-ponteH
2022-05-29 terminado v-slot-2020-suporte-CJVL53L0XV2
2022-05-29 terminado v-slot-2020-suporte-fuso-M8
2022-05-29 images da montagem
2022-05-29 att redame.md
2022-05-31 correção axis-cap
2022-05-31 att doc, arrumando arquivos
2022-05-31 correção doc (readme.md)
2022-06-01 criado suporte para base
2022-06-01 troca do suporte da camera
2022-06-01 att doc
2022-06-01 criado case para camera
2022-06-01 correção suporte-mesa-base
2022-06-01 att case camera
2022-06-01 correnção case camera
2022-06-01 correnção case-camera-tras
2022-06-01 removendo arquivos
2022-06-01 criado suporte-raspberrypi
2022-06-02 espaco para dissipador case-camera-tras
2022-06-02 cirado suporte-alca (alça)
2022-06-04 criado suporte-bateria
2022-06-05 inicio do desenvolvimento das firmware
2022-06-06 alterando suport-raspberry
2022-06-06 correção suport-raspberry
2022-06-06 criado suporte-NANO-BLE33S
2022-06-06 arrumand doc
2022-06-06 criado suporte-gps
2022-06-12 criado suporte-antena-gprs
2022-06-13 criado suporte-torre-instrumentos, iniciando configurações da rasp
2022-06-13 iniciando configurações da rasp
2022-06-13 criado suporte-pin
2022-06-13 fw rpi_pico
2022-06-15 testes dos motores
2022-06-15 Rede de conexão entre os sensores e dispositivos do trekking
2022-06-16 organizando arquivos do fw
2022-06-16 arrumando repo
2022-06-16 arrumando fw rpi_pico
2022-06-17 criado lib de uart para a fw RPI_PICO
2022-06-19 testes motores, por websoket
2022-06-20 cirando circuito
2022-06-21 circuiro rev 1.0
2022-06-21 circuiro rev 1.0 correção
2022-06-22 criado suporte-motorES
2022-06-23 mesa-base modificado para novo formato do robo
2022-06-27 criado axte-lidar
2022-06-27 mesa-base corrigido
2022-06-27 ATT placa fontes e pinos de contole
2022-06-30 att conexões dos motores, doc e firware
2022-07-08 testes PWM
2022-07-09 removendo fw RPI_PICO_INO
2022-07-10 controle + pwm rpi_pico
2022-08-07 fw com pico sdk
2022-08-11 FW RPI_PICO_SDK uart
2022-08-15 fw rpi-pico
2022-08-17 driver motor r001
2022-08-17 driver motor r002
2022-08-18 doc driver motor r002
2022-08-18 controle manual
2022-08-23 add doc
2022-09-20 correção build RPI_PICO_SDK
2022-09-20 correção build.sh
2022-09-21 remove builds
2022-09-21 add gitignore
2022-10-04 add imagens
2022-11-08 cpbr14
2022-11-21 gamepad2 + node-red
2022-12-03 suport-encoder
2022-12-03 update flow
2022-12-05 fwe d_motor_SDK tst pwm
2022-12-05 RPI_PICO_MPY descontinuado
2022-12-07 teste lib PID
2022-12-07 driver motor rev 2
2022-12-10 driver rasp-sense33
2022-12-10 driver rasp-sense33 enambe multecore
2022-12-11 driver rasp-sense33 comunicação serial ok
2022-12-11 flow node-RED adapitado para novo driver
2022-12-21 incluindo movimento
2023-01-17 correção AREF PCI
2023-01-17 GERBER
2023-02-11 migrando de raspberry para jetson nano
2023-02-12 arrumando gameped2 e reiando executavel
2023-02-16 uart1 pico ativada
2023-03-02 criando suspenção
2023-03-02 arrumando pecas
2023-03-31 atualização geral: lds, suspensão, caixa...
2023-04-13 pecas motor
2023-05-02 peças e alteraçõs para o motor novo
2023-05-10 peças tampa e motores
2023-07-18 palcas identificadoras, encoder, lidar, e configurações do sistema
2023-07-19 codigos gaamepad e ydlidar
2023-07-19 cpbr15 qrcode, FW habilitando leituras das fontes
2023-07-20 codigo display oled mostrador multimetro
2023-07-21 correção medidor/mostrador, add media movel e offset
2023-07-25 apresentacao CPBR15
2023-07-26 contole de estado de D2 a D9 do BLE SENSE 33 habilitado
2023-07-26 melhorando controle das saidas do sense33
2023-08-05 melhorias suspencao - quadro de suspencao
2023-08-06 ativando IMU
2023-08-15 update programa teste de aquisição
2023-09-25 ajuste camera FPV
2023-10-18 criando controle remoto
2023-11-04 Plataforma Eletrônica Para Controle Distribuído Em Rede
2023-11-28 PECDR update
2024-02-03 anotando correções em PECDR-W e criando programa de testes
2024-02-04 arrumando arquivos e documentação
2024-02-04 dog dos esquemas de alimentação e conexões gerais
2024-02-05 arrumando doc
2024-02-08 PECDR correção rs485 e de layout
2024-02-13 partes variadas da rv3
2024-02-29 testes com BESC
2024-06-27 correção de layout e conexões no circuito PECDR-W
2024-06-27 peças da versão 3 do robo
2024-06-27 atualizando arquivos do circuito PECDR-W
2024-06-27 atualização do esquema geral
2024-06-27 arrumando arquivos
2024-07-05 FW para PECDR motor/subsistemas, flow do nod-RED para comtrole, suporte para adapitador RS458
2024-07-08 imagem versão 3
2024-07-08 lincando apresentações no README.md inicial
2024-07-08 removendo arrumando arquivos
2024-07-09 att flow node-red para eventos
2024-08-03 iniciando voyager-rev04
2024-09-03 att rev 3 para 3.5
2024-11-04 arrumando firmware
2026-04-20 arrumando repo removendo *.FCBak
2026-04-20 antena-lateral
2026-04-20 cor base-inferio-165mm para roxo
2026-04-20 criando encaixe de bateria v2
2026-04-20 munando cor para roxo
2026-04-20 anotando cor da montage
2026-04-20 add suporte de lampada X1 v2
2026-04-20 carter v2
2026-04-20 nova fixação dos motores
2026-04-20 peças para montagem
2026-04-20 mudando cor da 'bandeira'
2026-04-20 arrumando puxador frontal
2026-04-20 arrumando suportes, e cores
